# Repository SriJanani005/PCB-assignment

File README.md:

View this project on [CADLAB.io](https://cadlab.io/project/29223). 

# PCB-assignment

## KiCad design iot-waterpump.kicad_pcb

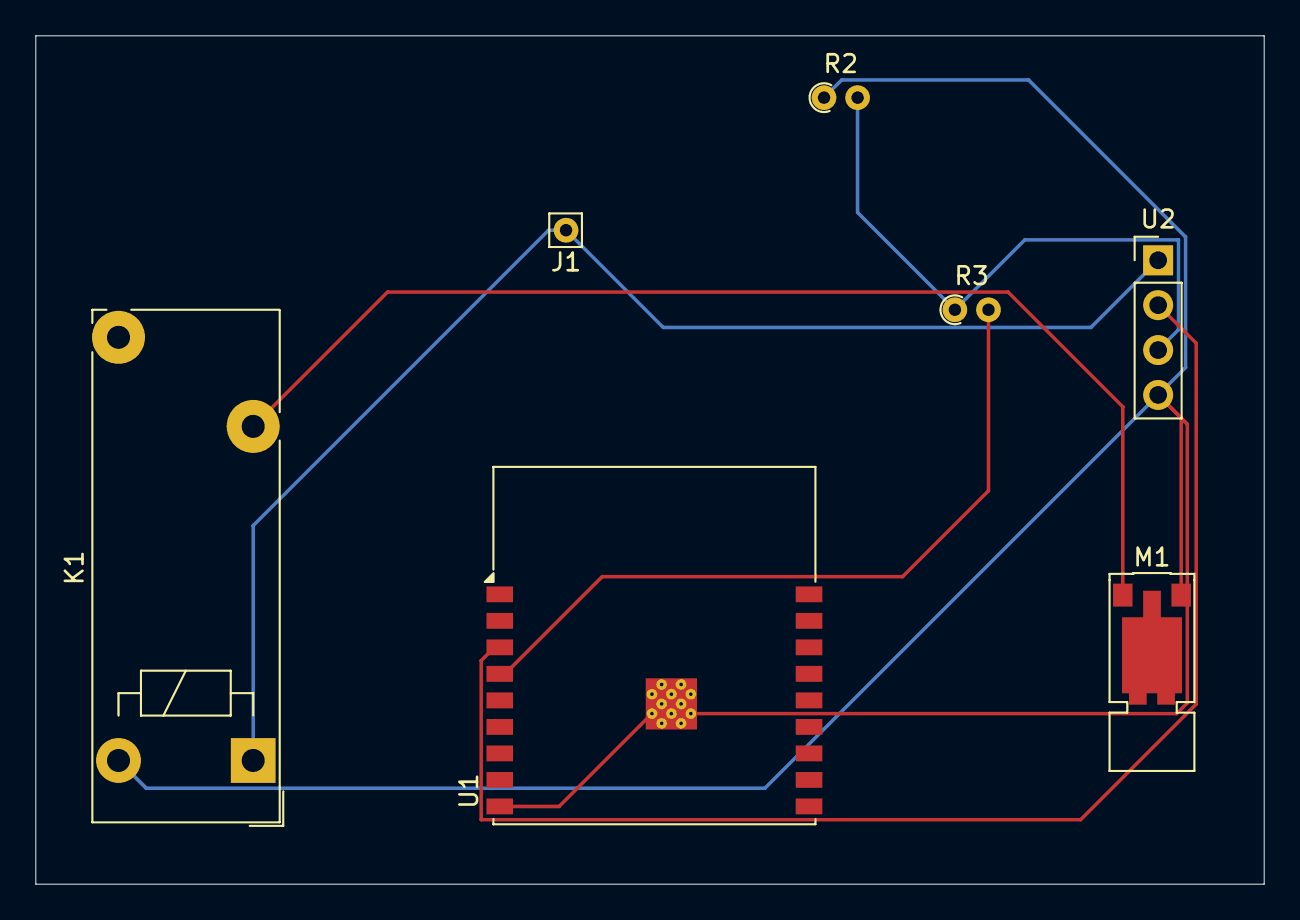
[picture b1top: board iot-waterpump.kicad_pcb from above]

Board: 2 copper layers, 69.5 x 48.0 mm, 7 parts (0 on the bottom side), 6 nets.

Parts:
J1: Conn_01x02; Pin_D0.7mm_L6.5mm_W1.8mm_FlatFork
K1: Relay_SPDT; Relay_1-Form-A_Schrack-RYII_RM5mm
M1: Motor_DC; Vybronics_VZ30C1T8219732L
R2, R3: R; R_Axial_DIN0204_L3.6mm_D1.6mm_P1.90mm_Vertical
U1: ESP32-C3-WROOM-02
U2: HC-SR04; PinHeader_1x04_P2.54mm_Vertical

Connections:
+5V: J1.1, K1.A1, U2.1 (VCC)
unnamed: K1.A2, M1.2 (-), R2.1, U1.9 (GND), U1.19 (GND), U2.4 (GND)
unnamed: K1.11, M1.1 (+)
unnamed: U1.3 (IO4), U2.2 (TRIG)
unnamed: R3.2, U1.4 (IO5)
unnamed: R2.2, R3.1, U2.3 (ECHO)

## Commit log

2025-04-09 pcb assignment
2025-04-09 Backlink to CADLAB.io has been added.
